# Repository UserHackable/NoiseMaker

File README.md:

## NoiseMaker 

### Board dimensions

* (140000, 120000) original units
* (1.4000, 1.2000) inches
* (35.5600, 30.4800) mm

| Front | Back |
| --- | --- |
|  |  |

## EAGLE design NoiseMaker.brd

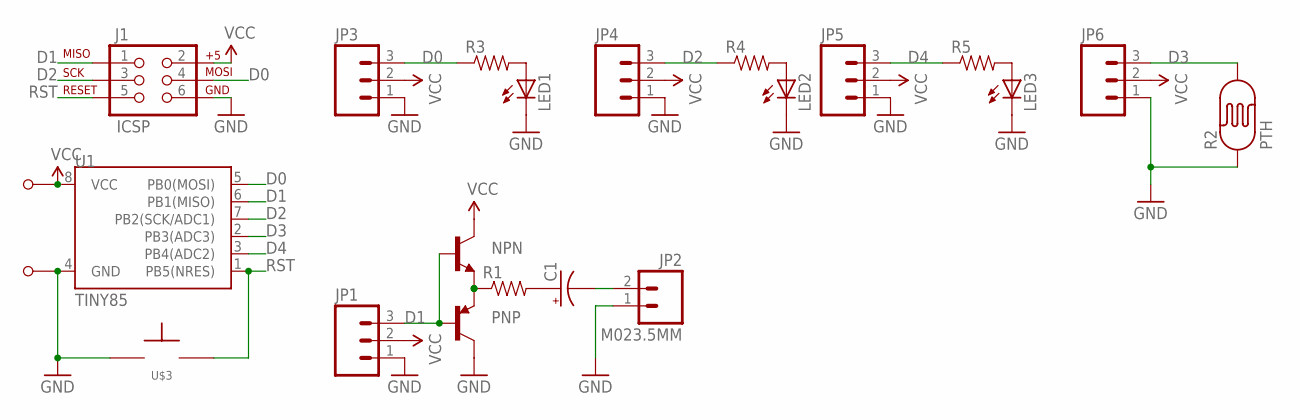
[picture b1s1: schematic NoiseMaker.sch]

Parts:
C1: CAP_POLPTH1; CPOL-RADIAL-100UF-25V
J1: ICSP; 2X3-NS
JP1, JP3, JP4, JP5, JP6: M03PTH; 1X03
JP2: M023.5MM; SCREWTERMINAL-3.5MM-2
LED1, LED2, LED3: LEDOVAL; LED-OVAL
NPN: TRANSISTOR_NPNTO-92-AMMO; TO-92-AMMO
PNP: TRANSISTOR_PNPAMMO; TO-92-AMMO
R1, R3, R4, R5: RESISTORAXIAL-0.3; AXIAL-0.3
R2: PTH; PHOTOCELL
U1: TINY85; DIP08
U$1, U$2: M1; M1_NO_STRAIN
U$3: TAC_SPST_NO

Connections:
D0: J1.4 (MOSI), JP3.3, R3.P$1 (1), U1.5 (PB0(MOSI))
D1: J1.1 (MISO), JP1.3, NPN.2 (B), PNP.2 (B), U1.6 (PB1(MISO))
D2: J1.3 (SCK), JP4.3, R4.P$1 (1), U1.7 (PB2(SCK/ADC1))
D3: JP6.3, R2.2, U1.2 (PB3(ADC3))
D4: JP5.3, R5.P$1 (1), U1.3 (PB4(ADC2))
GND: J1.6 (GND), JP1.1, JP2.1, JP3.1, JP4.1, JP5.1, JP6.1, LED1.CATHODE (C), LED2.CATHODE (C), LED3.CATHODE (C), PNP.3 (C), R2.1, U1.4 (GND), U$2.P$1, U$3.P$1
unnamed: LED1.ANODE (A), R3.P$2 (2)
unnamed: C1.1 (+), R1.P$2 (2)
unnamed: C1.2 (-), JP2.2
unnamed: LED2.ANODE (A), R4.P$2 (2)
unnamed: NPN.1 (E), PNP.1 (E), R1.P$1 (1)
unnamed: LED3.ANODE (A), R5.P$2 (2)
RST: J1.5 (RST), U1.1 (PB5(NRES)), U$3.P$2
VCC: J1.2 (V+), JP1.2, JP3.2, JP4.2, JP5.2, JP6.2, NPN.3 (C), U1.8 (VCC), U$1.P$1

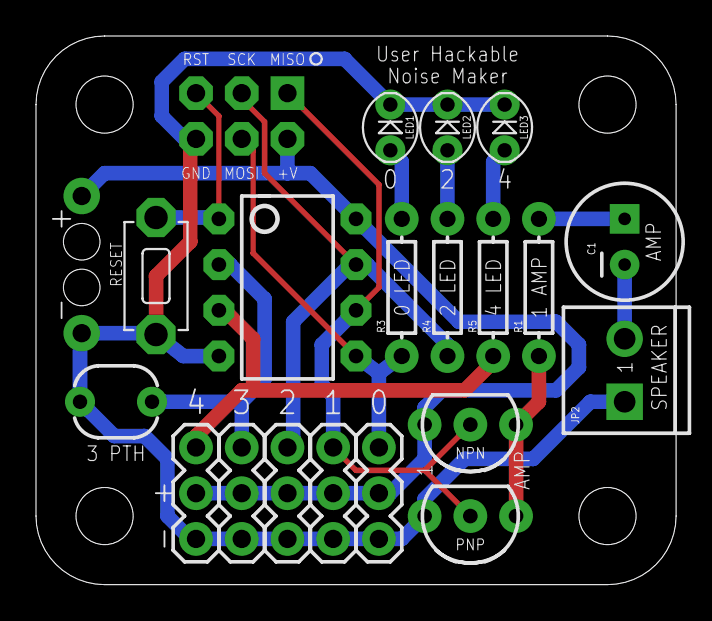
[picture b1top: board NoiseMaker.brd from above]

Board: 2 copper layers, 35.6 x 30.5 mm, 22 parts (0 on the bottom side), 14 nets.

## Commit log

2016-04-08 from Makefile

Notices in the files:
parts and their libraries:
SparkFun-Connectors: Licensing: Creative Commons ShareAlike 4.0 International - https://creativecommons.org/licenses/by-sa/4.0
